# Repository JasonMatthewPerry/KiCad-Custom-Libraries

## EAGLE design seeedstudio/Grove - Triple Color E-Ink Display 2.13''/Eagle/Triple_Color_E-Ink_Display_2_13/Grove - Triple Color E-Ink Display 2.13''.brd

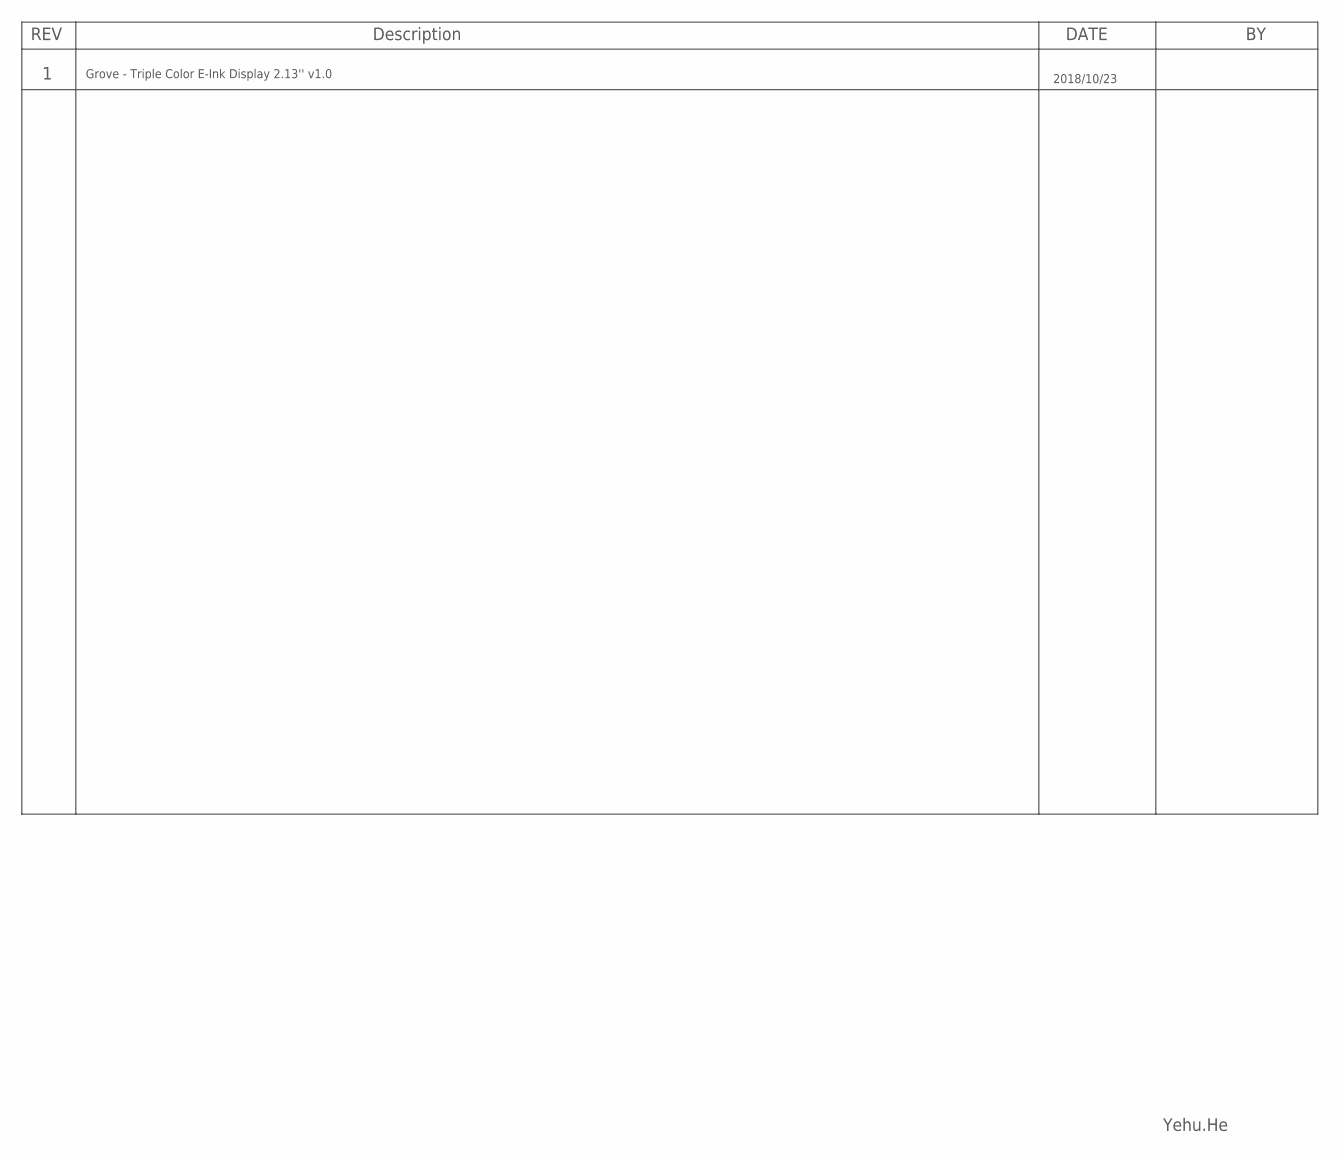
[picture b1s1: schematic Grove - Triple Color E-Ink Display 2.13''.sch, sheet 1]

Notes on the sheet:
Grove - Triple Color E-Ink Display 2.13'' v1.0
2018/10/23
Yehu.He

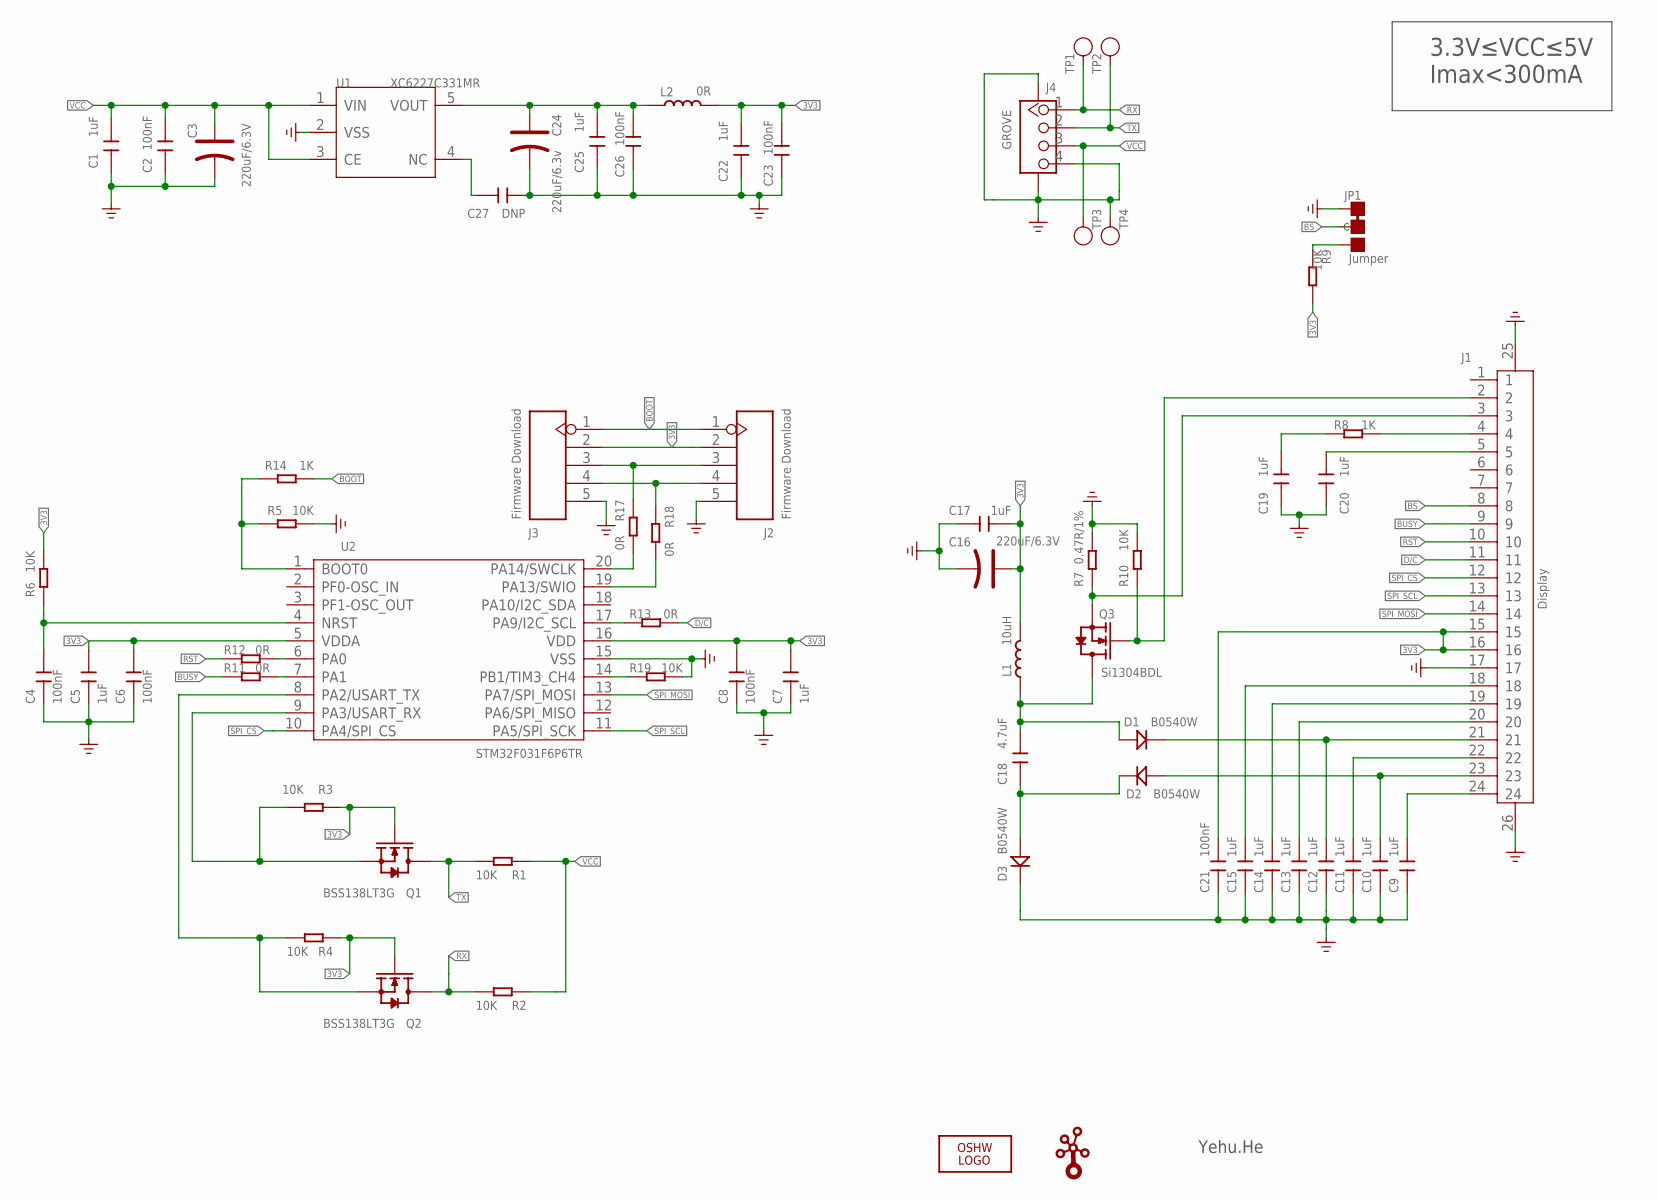
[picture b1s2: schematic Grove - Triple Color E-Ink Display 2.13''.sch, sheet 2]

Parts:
C1, C5, C7, C9, C10, C11, C12, C13, C14, C15, C17, C19, C20: 1uF; C0603
C2, C4, C6, C8, C21, C23, C26: 100nF; C0603
C3, C16: 220uF/6.3V; AVX-B
C18: 4.7uF; C0805
C22, C25: 1uF; C0805
C24: 220uF/6.3v; AVX-B
C27: DNP; C0603
D1, D2, D3: B0540W; SOD-323
J1: Display; FPCB24-SMD-0.5-17.6X5.0X2MM
J2, J3: Firmware Download; H5-SMD-2.54
J4: GROVE; HW4-SMD-2.0-90D
JP1: Jumper; 3P-SMD-SHORT
L1: 10uH; L5040S
L2: 0R; L0805
LOGO2: LOGO-OSHW-FILLX0200-NT; OSHW_FILLX200_NOTEXT
Q1, Q2: BSS138LT3G; SOT-323
Q3: Si1304BDL; SOT-323
R1, R2, R3, R4, R5, R6, R9, R10, R19: 10K; R0603
R7: 0.47R/1%; R0603
R8, R14: 1K; R0603
R11, R12, R13, R17, R18: 0R; R0603
TP1, TP2, TP3, TP4: Test; TP-D45MIL
U1: XC6227C331MR; SOT-23-5
U2: STM32F031F6P6TR; TSSOP20-0.65-6.5X4.4MM
U$20: LOGO-GROVE; GROVE-SILK-BIG

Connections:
3V3: C5.2, C6.2, C7.2, C8.2, C16.+, C17.1, C21.2, C22.2, C23.2, J1.15, J1.16, J2.2, J3.2, L1.2, L2.2, Q1.1 (G), Q2.1 (G), R3.2, R4.2, R6.1, R9.2, U2.5 (VDDA), U2.16 (VDD)
BOOT: J2.1, J3.1, R14.1
BS: J1.8, JP1.MM (C)
BUSY: J1.9, R11.1
D/C: J1.11, R13.1
GDR: J1.2, Q3.1 (G), R10.1
GND: C1.1, C2.1, C3.-, C4.1, C5.1, C6.1, C7.1, C8.1, C9.1, C10.1, C11.1, C12.1, C13.1, C14.1, C15.1, C16.-, C17.2, C19.2, C20.2, C21.1, C22.1, C23.1, C24.-, C25.1, C26.1, C27.1, D3.-, J1.17, J1.25 (P1), J1.26 (P2), J2.5, J3.5, J4.4, J4.SS1, J4.SS2, JP1.11 (L), R5.1, R7.2, R10.2, R19.1, TP4.T, U1.2 (VSS), U2.15 (VSS)
unnamed: R11.2, U2.7 (PA1)
unnamed: R12.2, U2.6 (PA0)
unnamed: R13.2, U2.17 (PA9/I2C_SCL)
unnamed: J2.3, J3.3, R17.1
unnamed: R5.2, R14.2, U2.1 (BOOT0)
unnamed: R19.2, U2.14 (PB1/TIM3_CH4)
unnamed: C27.2, U1.4 (NC)
unnamed: C4.2, R6.2, U2.4 (NRST)
unnamed: C18.1, D2.-, D3.+
unnamed: J2.4, J3.4, R18.1
unnamed: C18.2, D1.+, L1.1, Q3.3 (D)
unnamed: C19.1, R8.2
unnamed: R17.2, U2.20 (PA14/SWCLK)
unnamed: R18.2, U2.19 (PA13/SWIO)
unnamed: C15.2, J1.18
unnamed: C14.2, J1.19
unnamed: C13.2, J1.20
unnamed: C12.2, D1.-, J1.21
unnamed: C11.2, J1.22
unnamed: C10.2, D2.+, J1.23
unnamed: JP1.00 (R), R9.1
RESE: J1.3, Q3.2 (S), R7.1
RST: J1.10, R12.1
RX: J4.1, Q2.3 (D), R2.1, TP1.T
SCL_3V3: Q1.2 (S), R3.1, U2.9 (PA3/USART_RX)
SDA_3V3: Q2.2 (S), R4.1, U2.8 (PA2/USART_TX)
SPI_CS: J1.12, U2.10 (PA4/SPI_CS)
SPI_MOSI: J1.14, U2.13 (PA7/SPI_MOSI)
SPI_SCL: J1.13, U2.11 (PA5/SPI_SCK)
TX: J4.2, Q1.3 (D), R1.1, TP2.T
VCC: C1.2, C2.2, C3.+, J4.3, R1.2, R2.2, TP3.T, U1.1 (VIN), U1.3 (CE)
VCOM: C9.2, J1.24
VGH: C20.1, J1.5
VGL: J1.4, R8.1
VOUT: C24.+, C25.2, C26.2, L2.1, U1.5 (VOUT)

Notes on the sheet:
3.3V≤VCC≤5V Imax<300mA
Yehu.He

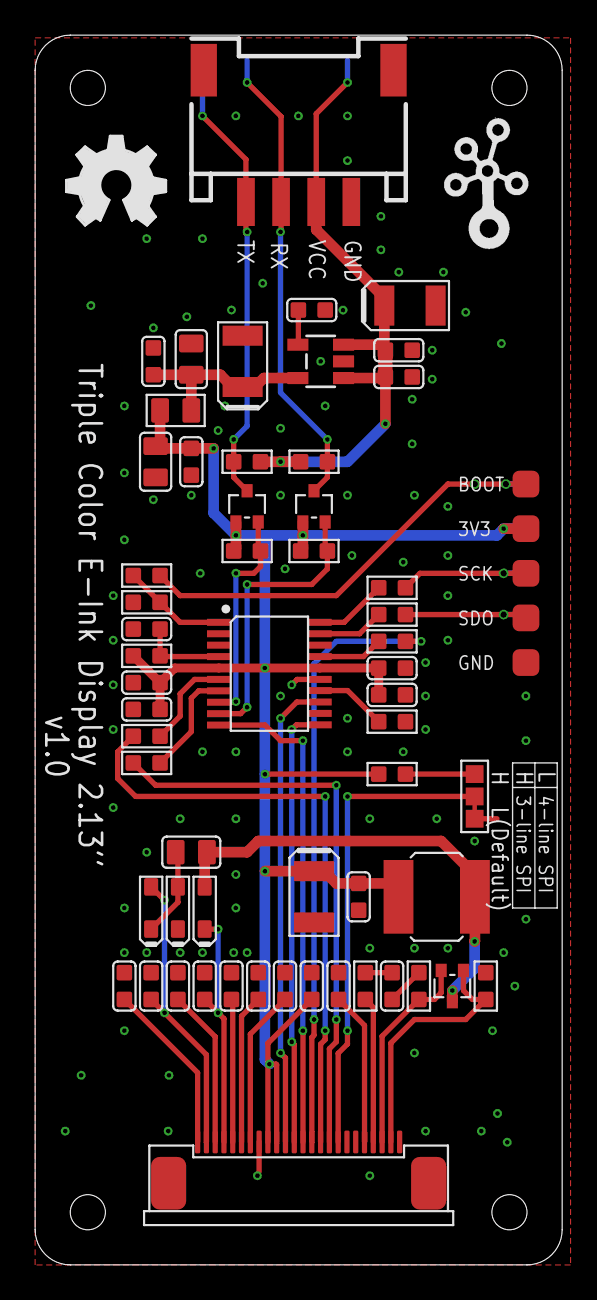
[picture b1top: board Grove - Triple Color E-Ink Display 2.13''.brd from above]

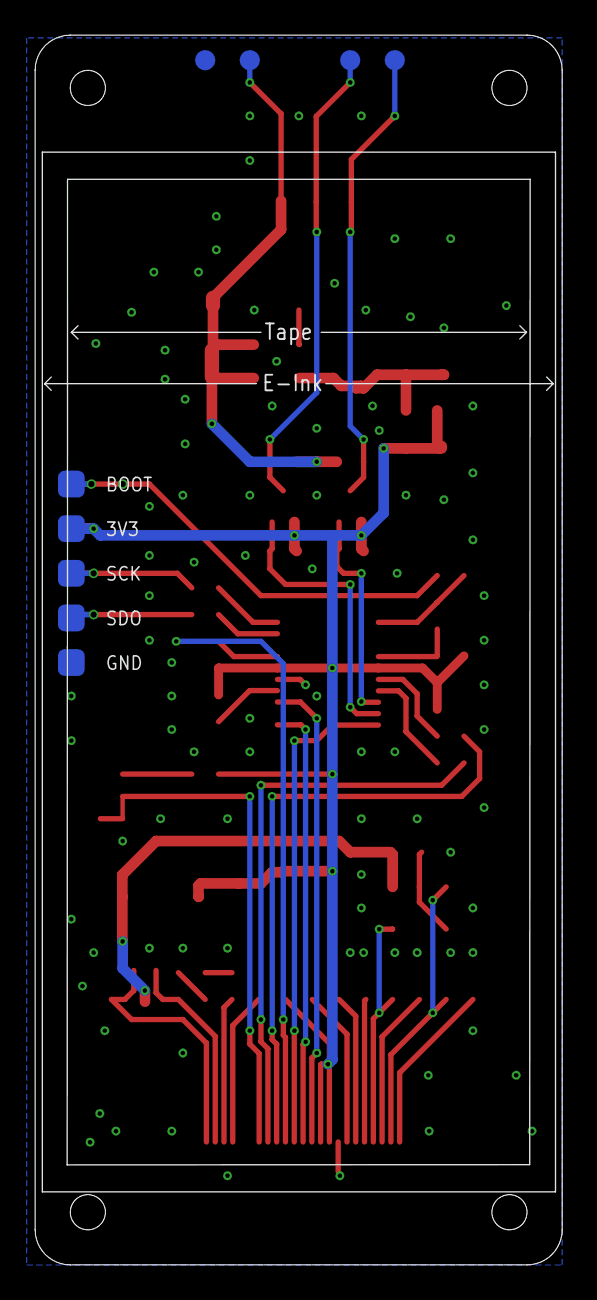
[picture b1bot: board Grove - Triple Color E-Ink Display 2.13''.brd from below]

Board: 2 copper layers, 30.0 x 70.0 mm, 65 parts (5 on the bottom side), 42 nets.

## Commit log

2020-07-28 Custom KiCad libraries created for ContainX. Updated ContainX V4 schematic and PCB layout.
2020-07-28 01 Custom Libraries:18650_With_Solder_Tab_SMB
2020-07-28 Added BMS footprint.
2020-07-28 Added spdt smd switches from digi.
2020-07-28 More V4 layout and 3d work.
2020-08-03 Added SMT 18650 battery.
2020-08-03 Update kicad custom libraries.
